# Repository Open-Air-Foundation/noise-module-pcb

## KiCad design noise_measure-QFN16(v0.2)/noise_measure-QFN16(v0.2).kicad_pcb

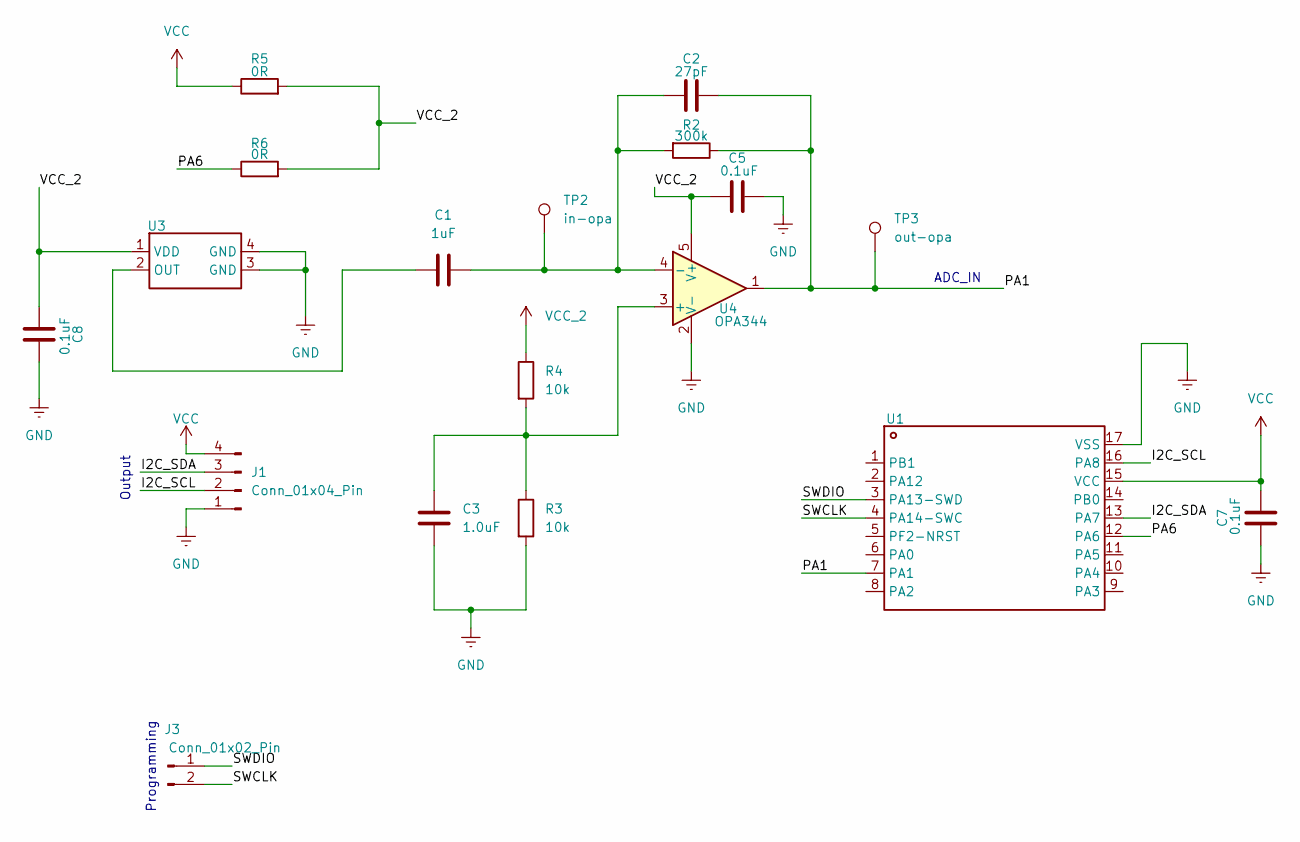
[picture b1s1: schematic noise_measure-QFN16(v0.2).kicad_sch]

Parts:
C1: 1uF; C_0402_1005Metric
C2: 27pF; C_0402_1005Metric
C3: 1.0uF; C_0402_1005Metric
C5, C7, C8: 0.1uF; C_0402_1005Metric
J1: Conn_01x04_Pin; PinHeader_1x04_P2.54mm_Horizontal
J3: Conn_01x02_Pin; PinHeader_1x02_P1.27mm_Vertical
R2: 300k; R_0402_1005Metric
R3, R4: 10k; R_0402_1005Metric
R5, R6: 0R; R_0402_1005Metric
TP2: in-opa; TestPoint_Pad_D1.0mm
TP3: out-opa; TestPoint_Pad_D1.0mm
U1: TQFN-16_L3.0-W3.0-P0.50-BL-EP1.7; Manufacturer Part PY32F002AW15U6TR; LCSC Part Name 32位微控制器 单片机 PY32F002AW15U6TR
U3: MIC-SMD_4P-L3.8-W3.0_LMA3729T421-OA1; Manufacturer Part LMA3729T381-OAS02; LCSC Part Name MEMSmic硅麦3729 上进音 s-38db±1 snr63db 语音阵列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
U4: OPA344; SOT-23-5

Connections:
/I2C_SCL: J1.2, U1.16 (PA8)
/I2C_SDA: J1.3, U1.13 (PA7)
/PA1: C2.1, R2.1, TP3.1 (1_1), U1.7 (PA1), U4.1
/PA6: R6.1, U1.12 (PA6)
/SWCLK: J3.2, U1.4 (PA14-SWC)
/SWDIO: J3.1, U1.3 (PA13-SWD)
GND: C3.2, C5.1, C7.2, C8.1, J1.1, R3.2, U1.17 (VSS), U3.3 (GND), U3.4 (GND), U4.2 (V-)
unnamed: C1.1, U3.2 (OUT)
unnamed: C3.1, R3.1, R4.2, U4.3 (+)
unnamed: C1.2, C2.2, R2.2, TP2.1 (1_1), U4.4 (-)
VCC: C7.1, J1.4, R5.1, U1.15 (VCC)
VCC_2: C5.2, C8.2, R4.1, R5.2, R6.2, U3.1 (VDD), U4.5 (V+)

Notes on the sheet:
Programming
ADC_IN
Output

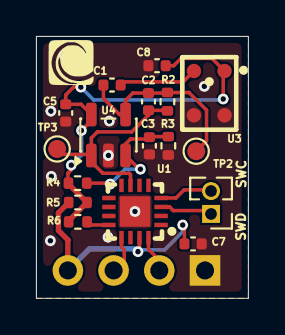
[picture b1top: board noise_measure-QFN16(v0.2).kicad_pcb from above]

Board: 2 copper layers, 11.8 x 14.6 mm, 18 parts (1 on the bottom side), 12 nets.

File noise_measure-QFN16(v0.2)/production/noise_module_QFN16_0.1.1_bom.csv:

Designator,Footprint,Quantity,Value,LCSC Part #
C1,0402,1,1uF,
C2,0402,1,27pF,
C3,0402,1,1.0uF,
"C5, C7, C8",0402,3,0.1uF,
J1,PinHeader_1x04_P2.54mm_Horizontal,1,Conn_01x04_Pin,
J3,PinHeader_1x02_P1.27mm_Vertical,1,Conn_01x02_Pin,
R2,0402,1,300k,
"R3, R4",0402,2,10k,
"R5, R6",0402,2,0R,
TP2,TestPoint_Pad_D1.0mm,1,in-opa,
TP3,TestPoint_Pad_D1.0mm,1,out-opa,
U1,TQFN-16_L3.0-W3.0-P0.50-BL-EP1.7,1,~,
U3,MIC-SMD_4P-L3.8-W3.0_LMA3729T421-OA1,1,~,
U4,SOT-23-5,1,OPA344,

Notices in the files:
noise_measure-QFN16(v0.2)/noise_measure-QFN16(v0.2).kicad_pcb:
CC-BY-SA
